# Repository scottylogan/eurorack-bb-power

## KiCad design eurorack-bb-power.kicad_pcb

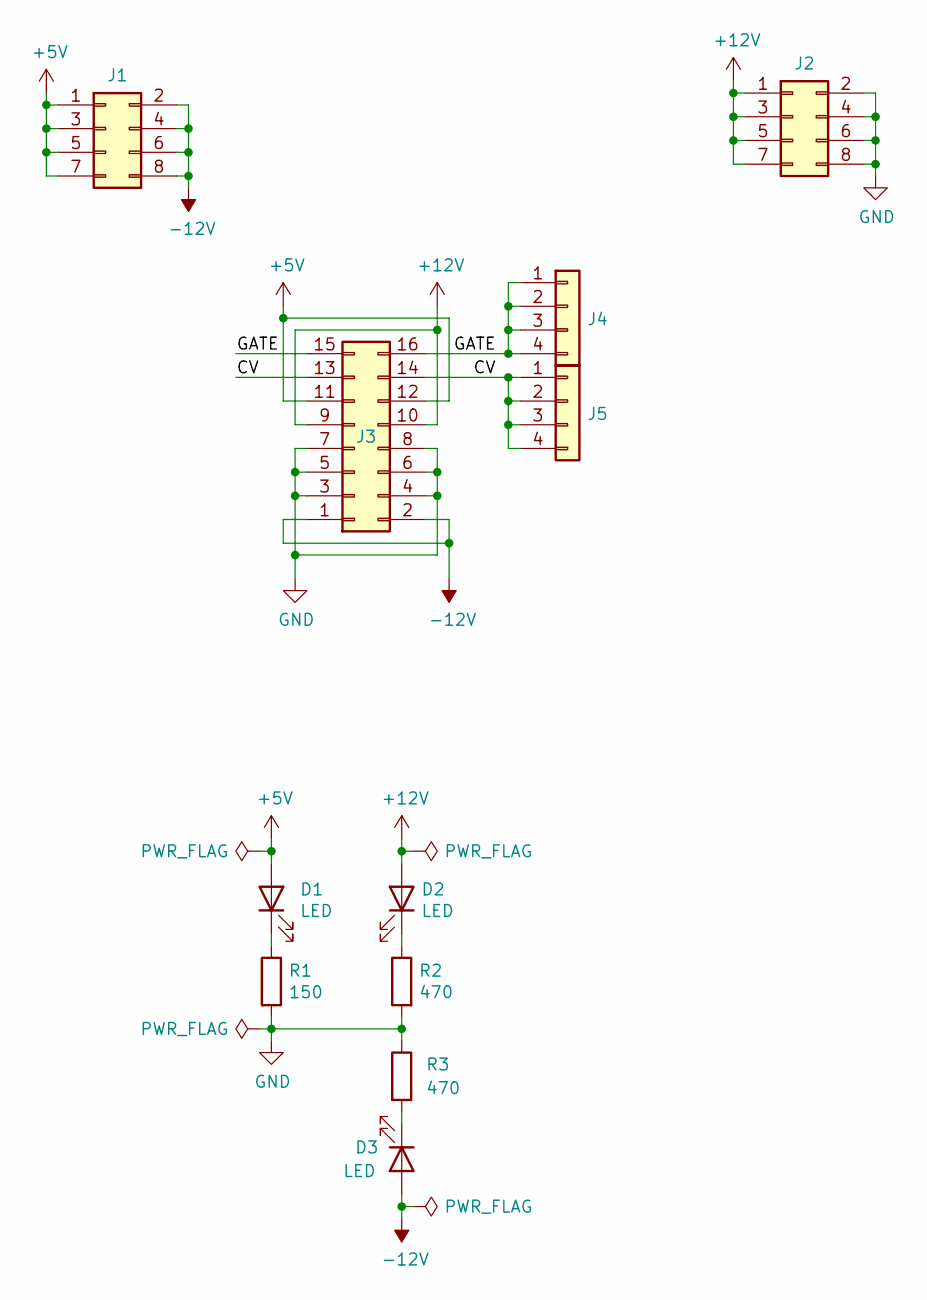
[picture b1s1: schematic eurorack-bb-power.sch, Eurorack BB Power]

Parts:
D1, D2, D3: LED; LED_1206_3216Metric_Pad1.42x1.75mm_HandSolder
J1, J2: Conn_02x04_Odd_Even; PinHeader_2x04_P2.54mm_Vertical
J3: Conn_02x08_Odd_Even; IDC-Header_2x08_P2.54mm_Vertical
J4, J5: Conn_01x04; PinSocket_1x04_P2.54mm_Vertical
R1: 150; R_1206_3216Metric_Pad1.42x1.75mm_HandSolder
R2, R3: 470; R_1206_3216Metric_Pad1.42x1.75mm_HandSolder

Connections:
+5V: D1.2 (A), J1.1, J1.3, J1.5, J1.7, J3.11, J3.12
+12V: D2.2 (A), J2.1, J2.3, J2.5, J2.7, J3.9, J3.10
-12V: D3.2 (A), J1.2, J1.4, J1.6, J1.8, J3.1, J3.2
/CV: J3.13, J3.14, J5.1, J5.2, J5.3, J5.4
/GATE: J3.15, J3.16, J4.1, J4.2, J4.3, J4.4
GND: J2.2, J2.4, J2.6, J2.8, J3.3, J3.4, J3.5, J3.6, J3.7, J3.8, R1.2, R2.2, R3.1
unnamed: D1.1 (K), R1.1
unnamed: D2.1 (K), R2.1
unnamed: D3.1 (K), R3.2

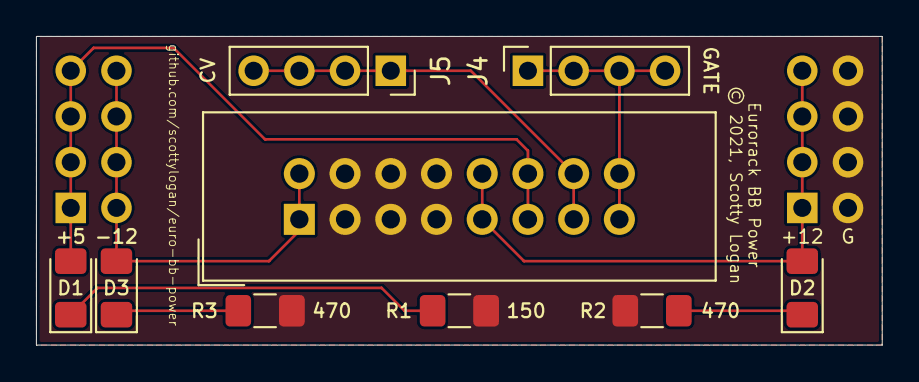
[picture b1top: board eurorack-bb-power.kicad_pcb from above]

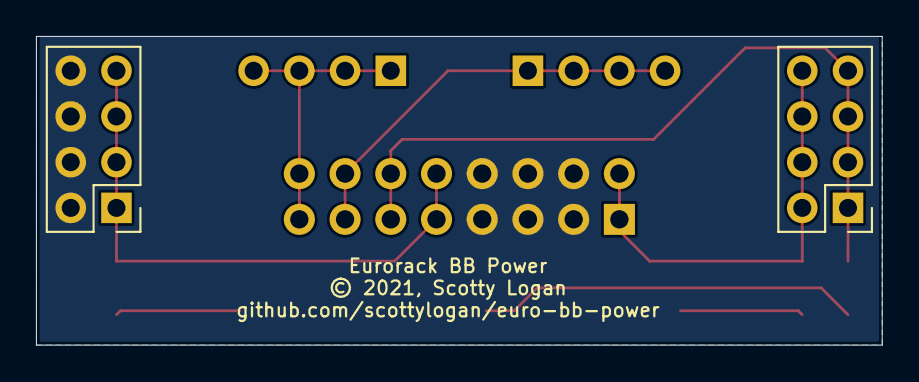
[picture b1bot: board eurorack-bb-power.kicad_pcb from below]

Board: 2 copper layers, 47.0 x 17.1 mm, 11 parts (2 on the bottom side), 9 nets.

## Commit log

2025-04-16 added LICENSE

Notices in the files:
eurorack-bb-power.kicad_pcb:
© 2021, Scotty Logan
